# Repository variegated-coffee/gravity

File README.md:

# Gravity

A scale module intended to be connected and powered via I2C

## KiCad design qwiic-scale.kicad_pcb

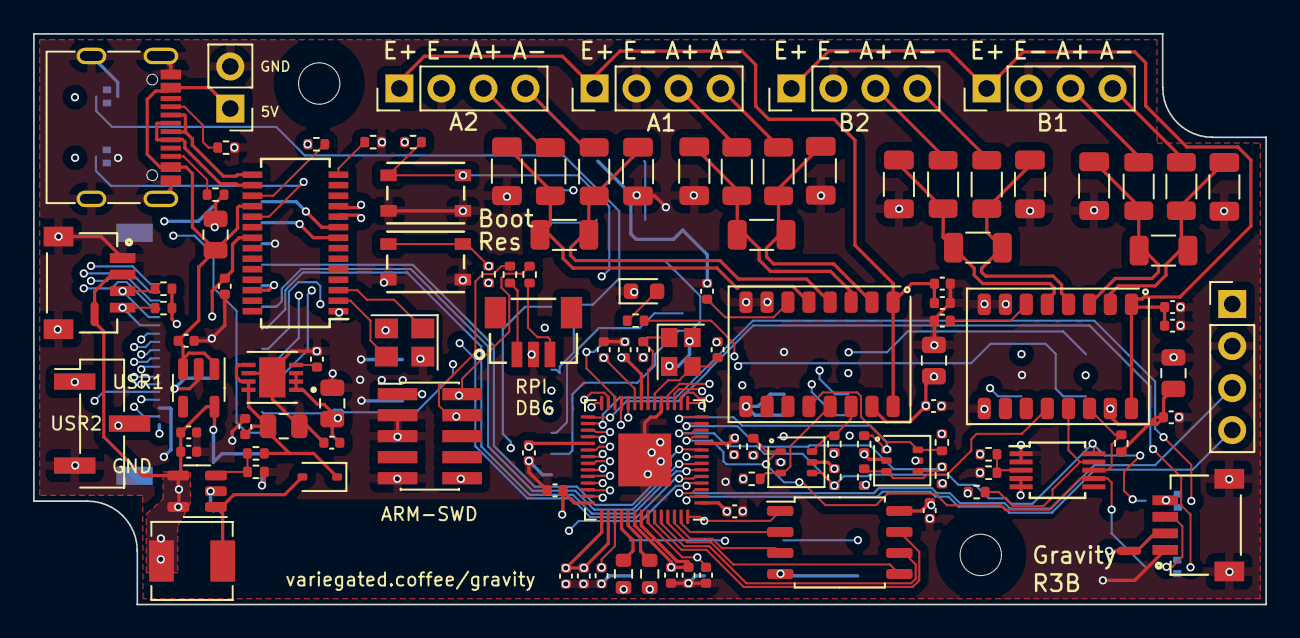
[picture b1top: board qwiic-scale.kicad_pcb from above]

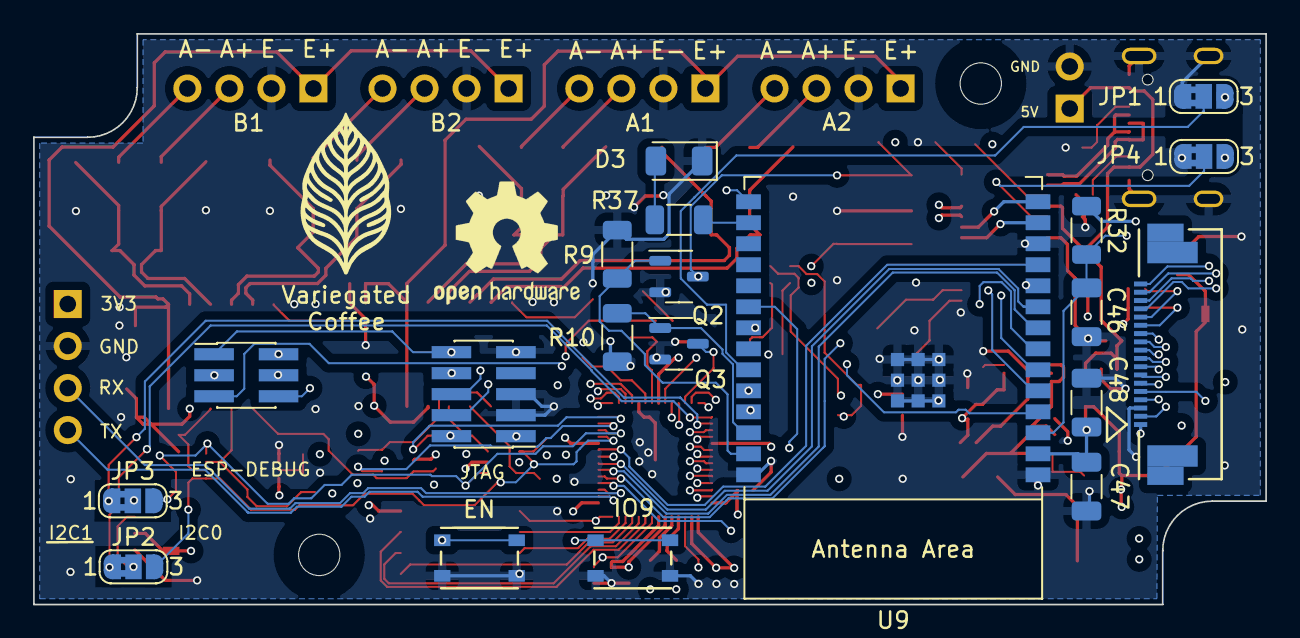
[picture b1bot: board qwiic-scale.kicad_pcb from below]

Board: 6 copper layers, 74.5 x 34.5 mm, 136 parts (20 on the bottom side), 112 nets.

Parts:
C1, C2: 12 pF; C_0402_1005Metric
C3, C14, C33, C35, C37, C38, C39, C41, C49, C50: 1 uF, >10V, X5R; C_0402_1005Metric
C4, C5, C6, C7, C8, C9, C10, C11, C12, C13, C15, C17, C18, C19, C40, C42, C44: 100 nF, >10V, X6S; C_0402_1005Metric
C16, C20, C34, C36, C43: 10 µF, >10V, X5R; C_0805_2012Metric
C21, C22, C27, C28: DNF; C_1206_3216Metric
C23, C24, C25, C29, C30, C31: 680 pF, C0G; C_1206_3216Metric
C26, C32: 100 nF, C0G; C_1206_3216Metric
C45: 1 nF; C_0402_1005Metric
C46: 1 uF, >6.3V, X5R; C_1206_3216Metric
C47: 100 nF, >10V, X6S; C_1206_3216Metric
C48: 22 uF, 6.3V, X5R; C_1206_3216Metric
D1: KT-0603W; LED_0603_1608Metric
D2: D_Schottky; D_SOD-323
D3: KT-1206R; LED_1206_3216Metric
H1, H2: MountingHole; MountingHole_2.5mm
J1: Molex 0527451897; CON_527461871_MOL
J2, J11: Conn_02x05_Odd_Even; PinHeader_2x05_P1.27mm_Vertical_SMD
J3, J4: SM04B-SRSS-TB(LF)(SN); JST_SM04B-SRSS-TB_LF__SN_
J5, J6, J7, J8, J10: Conn_01x04; PinHeader_1x04_P2.54mm_Vertical
J9: Conn_01x02; PinHeader_1x02_P2.54mm_Vertical
J12: Conn_02x03_Odd_Even; PinHeader_2x03_P1.27mm_Vertical_SMD
J13: BM03B-SRSS-TBLFSN; CONN_BM03B-SRSS-TBLFSN_JST
J14: USB_C_Receptacle_USB2.0; USB_C_Receptacle_G-Switch_GT-USB-7010ASV
J15: Conn_01x03; PinHeader_1x03_P2.54mm_Vertical_SMD_Pin1Left
JP1, JP2, JP3, JP4: SolderJumper_3_Bridged12; SolderJumper-3_P1.3mm_Bridged2Bar12_RoundedPad1.0x1.5mm_Num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
L1: 4.7 µH; L_Sunlord_MWSA0402S
NT1, NT2: NetTie_2; NetTie-2_SMD_Pad0.5mm
Q2, Q3: 2N7002; SOT-23-3
Q7, Q8: DMN63D8LDW; SOT-363_SC-70-6
R1, R3, R28: 4K7; R_0402_1005Metric
R2: 120R; R_0402_1005Metric
R4: 27K; R_0402_1005Metric
R5, R6: 27R; R_0603_1608Metric
R7, R8, R20, R21, R22, R23, R24, R25, R26, R27, R29, R30, R31, R36: 10K; R_0402_1005Metric
R9, R10, R32: 10K; R_1206_3216Metric
R11, R12, R15, R16: DNF; R_1206_3216Metric
R13, R14, R17, R18: 51R, Precision; R_1206_3216Metric
R19: 6K8; R_0402_1005Metric
R33, R34: 100R; R_0402_1005Metric
R35: 2K7 1%; R_0402_1005Metric
R37: 120R; R_1206_3216Metric
R38, R39: 5K1; R_0402_1005Metric
SW1, SW2, SW3, SW4: SW_Push; SW4_PTS815 SJM 250 SMTR LFS_CNK
U1: RP2040; QFN-56-1EP_7x7mm_P0.4mm_EP3.2x3.2mm
U2, U5: NAU7802SGI; SOP-16_4.4x10.4mm_P1.27mm
U3: AP3012; SOT-23-5
U4: LTC4316CMS_PBF; MSOP-10_3x3mm_P0.5mm
U6: TLV75733PDBVR; SOT-23-5
U7: ADM7170ACPZ-1.8-R7; SON50P300X300X80-9N
U8: FE1.1s (Rev B); SSOP-28_3.9x9.9mm_P0.635mm
U9: ESP32-C6-WROOM-1
U12: W25Q128JVS; SOIC-8_5.23x5.23mm_P1.27mm
Y1: XYDBPCNANF-12MHZ; Crystal_SMD_2520-4Pin_2.5x2.0mm
Y3: 12MHz; Crystal_SMD_3225-4Pin_3.2x2.5mm

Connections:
+3V3: C6.2, C7.2, C8.2, C9.2, C10.2, C11.2, C12.1, C13.1, C14.1, C15.2, C38.1, C39.1, C47.2, C48.2, C49.1, J1.1 (Vcc), J2.1, J10.1, J11.1, J12.2, JP1.3 (B), JP4.3 (B), L1.1, NT1.2, NT2.2, Q7.2 (G1), Q7.5 (G2), Q8.2 (G1), Q8.5 (G2), R1.2, R3.2, R7.1, R8.2, R20.1, R22.1, R24.1, R26.1, R30.1, R32.1, R36.2, U1.1 (IOVDD), U1.10 (IOVDD), U1.22 (IOVDD), U1.33 (IOVDD), U1.42 (IOVDD), U1.43 (ADC_AVDD), U1.44 (VREG_IN), U1.48 (USB_VDD), U1.49 (IOVDD), U3.4 (~SHDN), U3.5 (IN), U4.4 (VCC), U4.5 (ENABLE), U6.5 (OUT), U8.21 (VD33_O), U8.26 (OVCJ), U9.2 (3V3), U9.10 (GPIO8), U12.8 (VCC)
/RP2040_LED: R2.1, U1.8 (GPIO6)
/RP2040_USB_POST_R_DN: R6.1, U8.10 (DM1)
/RP2040_USB_POST_R_DP: R5.1, U8.11 (DP1)
AVCC: C16.2, C17.2, C20.1, C35.2, C42.2, C43.2, R21.1, R23.1, R25.1, R27.1, R29.1, R31.1, U2.15 (DVDD), U5.15 (DVDD), U7.1 (VOUT), U7.2 (VOUT), U7.3 (SENSE)
ESP32_BOOTSEL_RP2040: Q2.1 (G), R9.2, U9.27 (GPIO2/ADC1_CH2)
ESP32_DISABLE_RP2040: Q3.1 (G), R10.2, U9.26 (GPIO3/ADC1_CH3)
ESP32_EN: C46.2, J11.10, J12.1, R32.2, SW4.1, U9.3 (EN/CHIP_PU)
ESP32_GPIO9: J12.6, SW3.1, U9.15 (GPIO9)
ESP32_JTAG_SELECT: JP1.2 (C), U9.23 (GPIO15)
ESP32_TCK: J11.4, U9.6 (MTCK/GPIO6/ADC1_CH6)
ESP32_TDI: J11.8, U9.5 (MTDI/GPIO5/ADC1_CH5)
ESP32_TDO: J11.6, U9.7 (MTDO/GPIO7)
ESP32_TMS: J11.2, U9.4 (MTMS/GPIO4/ADC1_CH4)
ESP32_U0RXD: J12.5, U9.24 (U0RXD/GPIO17)
ESP32_U0TXD: J12.3, U9.25 (U0TXD/GPIO16)
ESP32_USB_DN: U8.8 (DM2), U9.13 (GPIO12/USB_D-)
ESP32_USB_DP: U8.9 (DP2), U9.14 (GPIO13/USB_D+)
EYESPI_BL: J1.2 (BACKLIGHT), U1.41 (GPIO29_ADC3)
EYESPI_BUSY_TE: J1.16 (BUSY/TE), U1.27 (GPIO16)
EYESPI_DC: J1.7 (DC), U1.37 (GPIO25)
EYESPI_DISP_CS: J1.9 (DISP_CS), U1.35 (GPIO23)
EYESPI_GP1: J1.17 (GPIO1), U1.17 (GPIO14)
EYESPI_GP2: J1.18 (GPIO2), U1.18 (GPIO15)
EYESPI_INT: J1.15 (INT), U1.28 (GPIO17)
EYESPI_MEM_CS: J1.11 (MEM_CS), U1.32 (GPIO21)
EYESPI_MISO: J1.6 (MISO), U1.40 (GPIO28_ADC2)
EYESPI_MOSI: J1.5 (MOSI), U1.39 (GPIO27_ADC1)
EYESPI_RES: J1.8 (RESET), U1.36 (GPIO24)
EYESPI_SCK: J1.4 (SCK), U1.38 (GPIO26_ADC0)
EYESPI_SD_CS: J1.10 (SD_CS), U1.34 (GPIO22)
EYESPI_TS_CS: J1.12 (TS_CS), U1.31 (GPIO20)
GND: C1.2, C2.2, C3.2, C4.2, C5.2, C6.1, C7.1, C8.1, C9.1, C10.1, C11.1, C12.2, C13.2, C14.2, C15.1, C16.1, C17.1, C18.1, C19.2, C20.2, C21.1, C22.2, C24.1, C25.2, C27.1, C28.2, C30.1, C31.2, C33.1, C34.2, C35.1, C36.2, C37.1, C38.2, C39.2, C40.1, C41.1, C42.1, C43.1, C44.2, C45.2, C46.1, C47.1, C48.1, C49.2, C50.2, D1.1 (K), D3.1 (K), J1.3 (GND), J2.3, J2.5, J2.9, J3.1, J3.S1 (SHIELD), J3.S2 (SHIELD), J4.1, J4.S1 (SHIELD), J4.S2 (SHIELD), J5.2, J6.2, J7.2, J8.2, J9.2, J10.2, J11.3, J11.5, J11.9, J12.4, J13.2, J14.A1 (GND), J14.A12 (GND), J14.B1 (GND), J14.B12 (GND), J14.S1 (SHIELD), J15.3, JP1.1 (A), JP4.1 (A), Q2.2 (S), Q3.2 (S), R9.1, R10.1, R19.2, R28.2, R35.1, R38.2, R39.2, SW1.2, SW2.2, SW3.2, SW4.2, U1.19 (TESTEN), U1.57 (GND), U2.7 (REFN), U2.8 (AVSS), U2.9 (DVSS), U3.2 (GND), U4.1 (GND), U4.2 (XORH), U5.7 (REFN), U5.8 (AVSS), U5.9 (DVSS), U6.2 (GND), U7.6 (GND), U7.9 (EXP), U8.1 (VSS), U9.1 (GND), U9.12 (GPIO11), U9.28 (GND), U9.29 (GND), U12.4 (GND), Y1.2, Y1.4, Y3.2, Y3.4
LOAD_CELL_ADC1_1_N: C25.1, C26.2, R14.2, U2.2 (VIN1N)
LOAD_CELL_ADC1_1_P: C24.2, C26.1, R13.2, U2.3 (VIN1P)
LOAD_CELL_ADC1_2_N: C22.1, C23.2, R12.2, U2.4 (VIN2N)
LOAD_CELL_ADC1_2_P: C21.2, C23.1, R11.2, U2.5 (VIN2P)
LOAD_CELL_ADC2_1_N: C31.1, C32.2, R18.2, U5.2 (VIN1N)
LOAD_CELL_ADC2_1_P: C30.2, C32.1, R17.2, U5.3 (VIN1P)
LOAD_CELL_ADC2_2_N: C28.1, C29.2, R16.2, U5.4 (VIN2N)
LOAD_CELL_ADC2_2_P: C27.2, C29.1, R15.2, U5.5 (VIN2P)
NAU7802_1_AVDD: C18.2, C37.2, J5.1, J6.1, U2.1 (REFP), U2.16 (AVDD/LDO)
NAU7802_1_DRDY_3V3: Q8.1 (S1), R24.2, U1.14 (GPIO11)
NAU7802_1_DRDY_5V: Q8.6 (D1), R25.2, U2.12 (DRDY)
NAU7802_1_SCLK_3V3: JP3.3 (B), Q7.4 (S2), R22.2, U1.12 (GPIO9), U4.10 (SCLIN)
NAU7802_1_SCLK_5V: Q7.3 (D2), R23.2, U2.13 (SCLK)
NAU7802_1_SDIO_3V3: JP2.3 (B), Q7.1 (S1), R20.2, U1.11 (GPIO8), U4.7 (SDAIN)
NAU7802_1_SDIO_5V: Q7.6 (D1), R21.2, U2.14 (SDIO)
NAU7802_2_AVDD: C40.2, C41.2, J7.1, J8.1, U5.1 (REFP), U5.16 (AVDD/LDO)
NAU7802_2_DRDY_3V3: Q8.4 (S2), R30.2, U1.13 (GPIO10)
NAU7802_2_DRDY_5V: Q8.3 (D2), R31.2, U5.12 (DRDY)
NAU7802_2_SCLK_5V: R29.2, U4.9 (SCLOUT), U5.13 (SCLK)
NAU7802_2_SDIO_5V: R27.2, U4.8 (SDAOUT), U5.14 (SDIO)
unnamed: D1.2 (A), R2.2
unnamed: D2.2 (A), L1.2, U3.1 (SW)
unnamed: C33.2, C34.1, D2.1 (K), R4.1, U7.5 (EN), U7.7 (VIN), U7.8 (VIN)
unnamed: D3.2 (A), R37.2
unnamed: J5.3, R11.1
unnamed: J5.4, R12.1
unnamed: J6.3, R13.1
unnamed: J6.4, R14.1
unnamed: J7.3, R15.1
unnamed: J7.4, R16.1
unnamed: J8.3, R17.1
unnamed: J8.4, R18.1
unnamed: J13.1, R33.2
unnamed: J13.3, R34.1
unnamed: J14.A5 (CC1), R39.1
unnamed: J14.B5 (CC2), R38.1
unnamed: J4.3, JP2.2 (C)
unnamed: J4.4, JP3.2 (C)
unnamed: JP4.2 (C), U8.19 (BUSJ)
unnamed: C3.1, C4.1, C5.1, U1.23 (DVDD), U1.45 (VREG_VOUT), U1.50 (DVDD)
unnamed: C1.1, U1.20 (XIN), Y1.3
unnamed: C2.1, U1.21 (XOUT), Y1.1
unnamed: C44.1, U2.6 (VBG)
unnamed: R4.2, R19.1, U3.3 (FB)
unnamed: R26.2, R28.1, U4.3 (XORL)
unnamed: C19.1, U5.6 (VBG)
unnamed: C45.1, U7.4 (SS)
unnamed: R35.2, U8.14 (REXT)
unnamed: U8.3 (XIN), Y3.1
unnamed: U8.2 (XOUT), Y3.3
unnamed: R36.1, U8.17 (~XRSTJ)
unnamed: R37.1, U9.16 (GPIO18)
QWIIC_SCL: J1.13 (SCL), J3.4, JP3.1 (A), R8.1, U1.30 (GPIO19)
QWIIC_SDA: J1.14 (SDA), J3.3, JP2.1 (A), R7.2, U1.29 (GPIO18)
QWIIC_VIN1: J3.2, NT1.1
QWIIC_VIN2: J4.2, NT2.1
RP2040_BOOTSEL: Q2.3 (D), R3.1, SW1.1, U1.56 (QSPI_SS), U12.1 (~CS)
RP2040_ESP32_GP1: U1.4 (GPIO2), U9.20 (GPIO22)
RP2040_ESP32_GP2: U1.5 (GPIO3), U9.21 (GPIO23)
RP2040_ESP32_RX: U1.7 (GPIO5), U9.9 (GPIO1/ADC1_CH1/XTAL_32K_N)
RP2040_ESP32_TX: U1.6 (GPIO4), U9.8 (GPIO0/ADC1_CH0/XTAL_32K_P)
RP2040_QSPI_SCK: U1.52 (QSPI_SCLK), U12.6 (CLK)
RP2040_QSPI_SD0: U1.53 (QSPI_SD0), U12.5 (DI(IO0))
RP2040_QSPI_SD1: U1.55 (QSPI_SD1), U12.2 (DO(IO1))
RP2040_QSPI_SD2: U1.54 (QSPI_SD2), U12.3 (IO2)
RP2040_QSPI_SD3: U1.51 (QSPI_SD3), U12.7 (IO3)
RP2040_RESETn: J2.10, Q3.3 (D), R1.1, SW2.1, U1.26 (RUN)
RP2040_SERIAL_BOOT: U1.9 (GPIO7), U9.11 (GPIO10)
RP2040_SWCLK: J2.4, R33.1, U1.24 (SWCLK)
RP2040_SWD: J2.2, R34.2, U1.25 (SWD)
RP2040_UART0_RX: J10.3, U1.3 (GPIO1)
RP2040_UART0_TX: J10.4, U1.2 (GPIO0)
RP2040_USB_PRE_R_DN: R6.2, U1.46 (USB_DM)
RP2040_USB_PRE_R_DP: R5.2, U1.47 (USB_DP)
USB_UPSTREAM_DN: J14.A7 (D-), J14.B7 (D-), U8.15 (DMU)
USB_UPSTREAM_DP: J14.A6 (D+), J14.B6 (D+), U8.16 (DPU)
USB_VBUS: C36.1, C50.1, J9.1, J14.A4 (VBUS), J14.A9 (VBUS), J14.B4 (VBUS), J14.B9 (VBUS), U6.1 (IN), U6.3 (EN), U8.18 (VBUSM)
USER_1: J15.1, U1.16 (GPIO13)
USER_2: J15.2, U1.15 (GPIO12)

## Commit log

2024-06-10 Initial import
2024-06-10 Added R0A as sent to manufacturer
2024-06-10 Add .gitignore
2024-06-10 Add license
2024-06-30 R1A updates
2024-09-04 Final version sent to manufacturing
2024-09-04 Add R2A manufacturing data
2025-03-24 Add production files for R3B
